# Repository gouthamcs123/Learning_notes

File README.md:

# Learning_notes
Documentation of what i studied during my training period

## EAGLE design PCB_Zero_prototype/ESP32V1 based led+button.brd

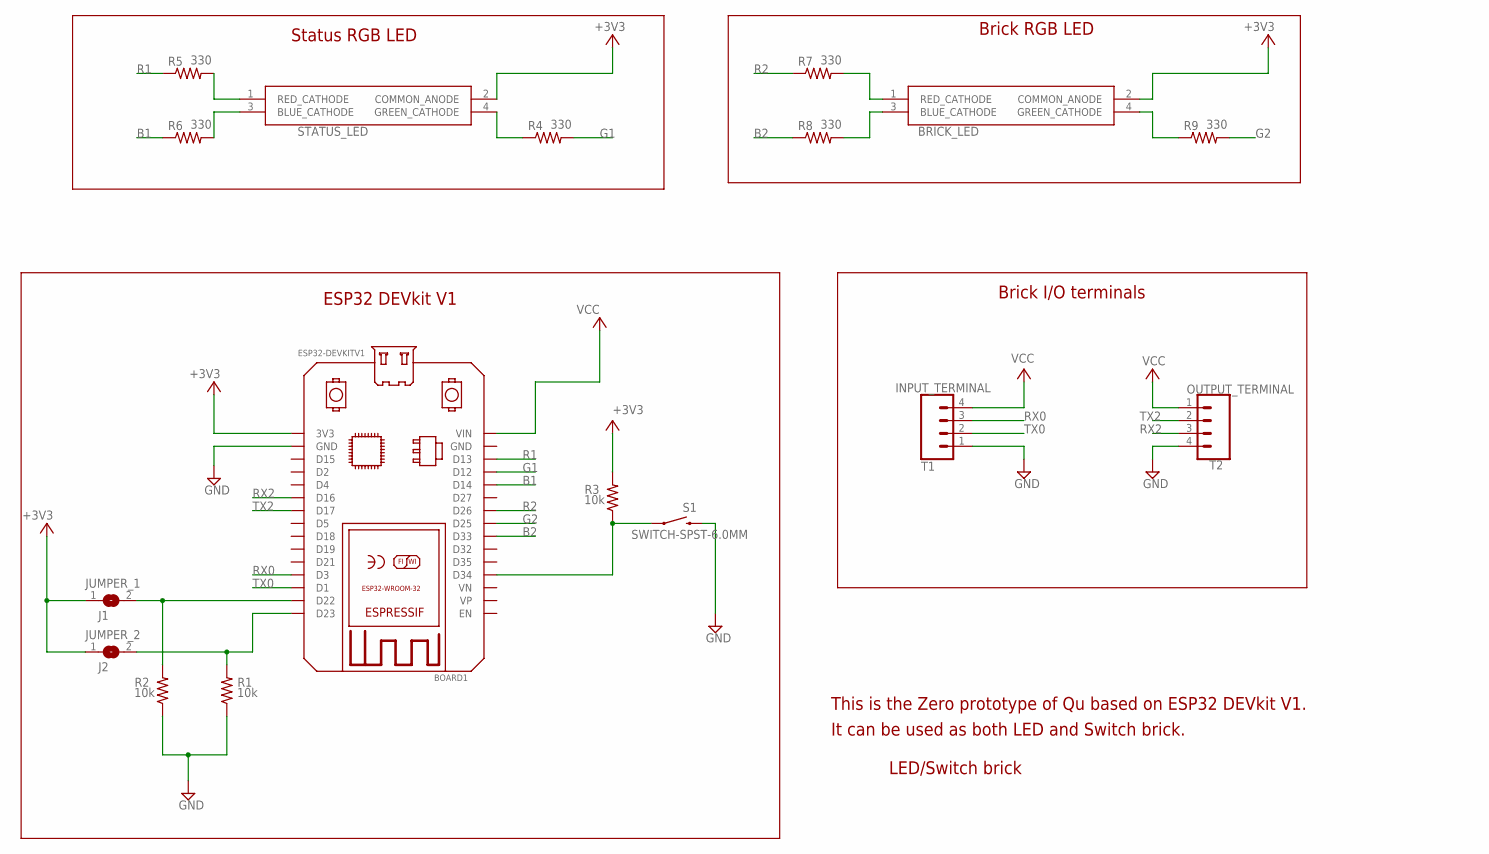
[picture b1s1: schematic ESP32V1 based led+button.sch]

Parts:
BOARD1: ESP32DEVKITV1; ESP32-DEVKITV1
BRICK_LED: WP154A4SEJ3VBDZGW_CA; L-154A4SUREQBFZGEC
INPUT_TERMINAL: T1; 1X04
JUMPER_1: J1; SJW
JUMPER_2: J2; SJW
OUTPUT_TERMINAL: T2; 1X04
R1, R2, R3: 10k; AXIAL-0.3
R4, R5, R6, R7, R8, R9: 330; AXIAL-0.3
S1: SWITCH-SPST-6.0MM; TACTILE_SWITCH_PTH_6.0MM_KIT
STATUS_LED: WP154A4SEJ3VBDZGW_CA; L-154A4SUREQBFZGEC

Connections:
+3V3: BOARD1.3V3, BRICK_LED.2 (COMMON_ANODE), JUMPER_1.1, JUMPER_2.1, R3.P$2 (2), STATUS_LED.2 (COMMON_ANODE)
B1: BOARD1.D14, R6.P$1 (1)
B2: BOARD1.D33, R8.P$1 (1)
G1: BOARD1.D12, R4.P$2 (2)
G2: BOARD1.D25, R9.P$2 (2)
GND: BOARD1.GND@1 (GND), INPUT_TERMINAL.1, OUTPUT_TERMINAL.4, R1.P$1 (1), R2.P$1 (1), S1.3 (2)
unnamed: BOARD1.D22, JUMPER_1.2, R2.P$2 (2)
unnamed: BOARD1.D23, JUMPER_2.2, R1.P$2 (2)
unnamed: R6.P$2 (2), STATUS_LED.3 (BLUE_CATHODE)
unnamed: R5.P$2 (2), STATUS_LED.1 (RED_CATHODE)
unnamed: BOARD1.D34, R3.P$1 (1), S1.1
unnamed: R4.P$1 (1), STATUS_LED.4 (GREEN_CATHODE)
unnamed: BRICK_LED.3 (BLUE_CATHODE), R8.P$2 (2)
unnamed: BRICK_LED.1 (RED_CATHODE), R7.P$2 (2)
unnamed: BRICK_LED.4 (GREEN_CATHODE), R9.P$1 (1)
R1: BOARD1.D13, R5.P$1 (1)
R2: BOARD1.D26, R7.P$1 (1)
RX0: BOARD1.D3, INPUT_TERMINAL.3
RX2: BOARD1.D16, OUTPUT_TERMINAL.3
TX0: BOARD1.D1, INPUT_TERMINAL.2
TX2: BOARD1.D17, OUTPUT_TERMINAL.2
VCC: BOARD1.VIN, INPUT_TERMINAL.4, OUTPUT_TERMINAL.1

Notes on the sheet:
LED/Switch brick
This is the Zero prototype of Qu based on ESP32 DEVkit V1.
It can be used as both LED and Switch brick.
Brick I/O terminals
Status RGB LED
Brick RGB LED
ESP32 DEVkit V1

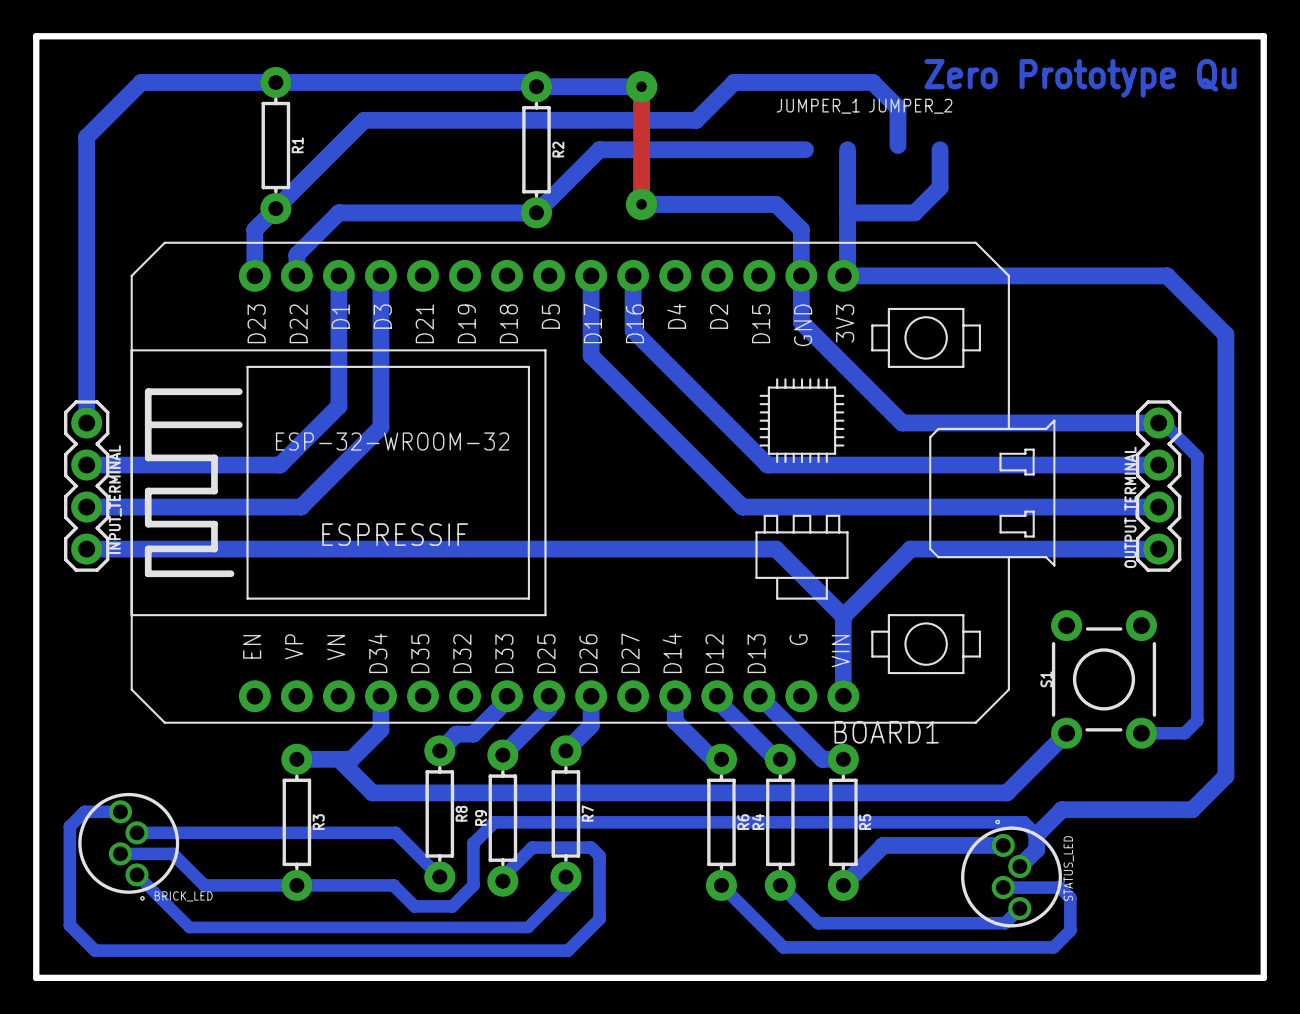
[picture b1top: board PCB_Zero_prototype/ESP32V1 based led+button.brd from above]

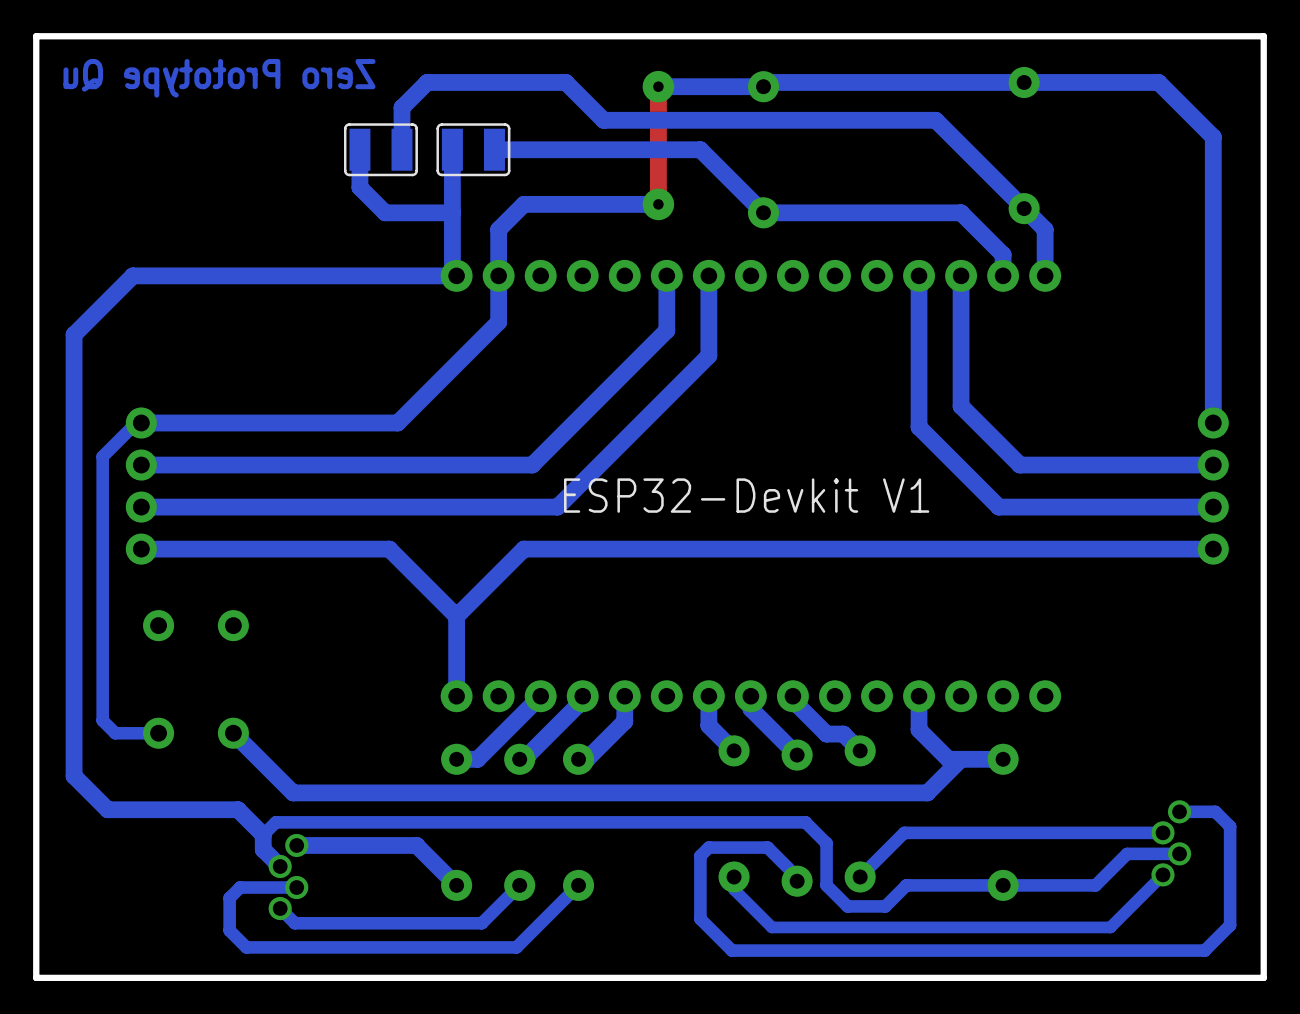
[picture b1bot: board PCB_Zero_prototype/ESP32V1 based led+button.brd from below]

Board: 2 copper layers, 74.2 x 56.9 mm, 17 parts (2 on the bottom side), 22 nets.

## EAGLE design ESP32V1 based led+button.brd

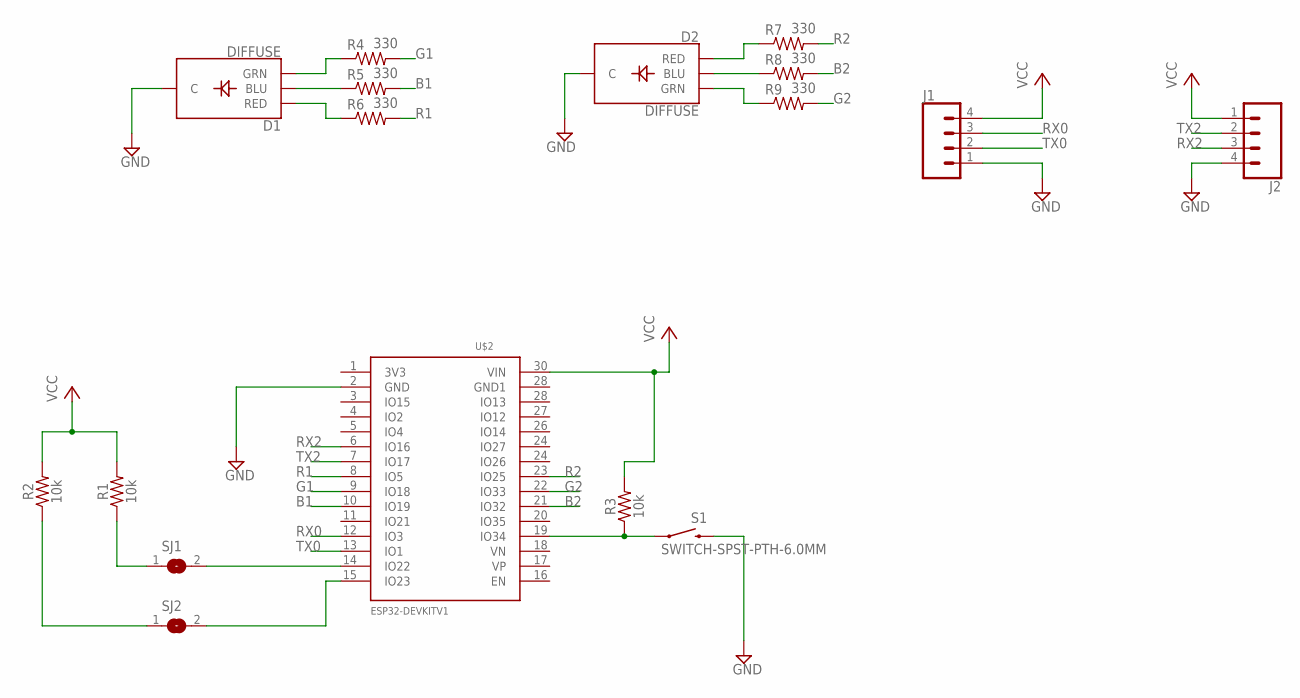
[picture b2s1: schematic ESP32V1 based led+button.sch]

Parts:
D1, D2: DIFFUSE; LED-RGB-THRU
J1, J2: CONN_04; 1X04
R1, R2, R3: 10k; AXIAL-0.3
R4, R5, R6, R7, R8, R9: 330; AXIAL-0.3
S1: SWITCH-SPST-PTH-6.0MM; TACTILE_SWITCH_PTH_6.0MM_KIT
SJ1, SJ2: SJW
U$2: ESP32DEVKITV1; ESP32-DEVKITV1

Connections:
B1: R5.P$2 (2), U$2.10 (IO19)
B2: R8.P$2 (2), U$2.21 (IO32)
G1: R4.P$2 (2), U$2.9 (IO18)
G2: R9.P$2 (2), U$2.22 (IO33)
GND: D1.2 (C), D2.2 (C), J1.1, J2.4, S1.3 (2), U$2.2 (GND)
unnamed: SJ2.2, U$2.15 (IO23)
unnamed: R2.P$1 (1), SJ2.1
unnamed: SJ1.2, U$2.14 (IO22)
unnamed: R1.P$1 (1), SJ1.1
unnamed: D1.3 (GRN), R4.P$1 (1)
unnamed: D1.4 (BLU), R5.P$1 (1)
unnamed: D1.1 (RED), R6.P$1 (1)
unnamed: D2.4 (BLU), R8.P$1 (1)
unnamed: R3.P$1 (1), S1.1, U$2.19 (IO34)
unnamed: D2.1 (RED), R7.P$1 (1)
unnamed: D2.3 (GRN), R9.P$1 (1)
R1: R6.P$2 (2), U$2.8 (IO5)
R2: R7.P$2 (2), U$2.23 (IO25)
RX0: J1.3, U$2.12 (IO3)
RX2: J2.3, U$2.6 (IO16)
TX0: J1.2, U$2.13 (IO1)
TX2: J2.2, U$2.7 (IO17)
VCC: J1.4, J2.1, R1.P$2 (2), R2.P$2 (2), R3.P$2 (2), U$2.30 (VIN)

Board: 2 copper layers, 17 parts (0 on the bottom side), 23 nets, no tracks yet.

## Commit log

2020-11-21 new file added
2020-11-21 heading code ettiquote added
2020-11-21 added file
2020-11-21 added about code etiquette
2020-11-21 version control heading
2020-11-21 software used
2020-11-21 eagle
2020-11-21 arduino
2020-11-22 added points
2020-11-22 added intro about edge connectors
2020-11-22 added content
2020-11-22 images added
2020-11-23 added
2020-11-23 added more connectors
2020-11-23 new file about work
2020-11-25 added image
2020-11-25 added files
2020-11-26 added data and files
2020-11-26 spring fingers deleted
2020-11-26 file again added
2020-11-26 added connector datasheet from TE connectivity
2020-11-27 added...
2020-11-30 documented
2020-11-30 edited and documented
2020-12-01 edited
2020-12-02 renamed file
2020-12-02 Delete anr.docx
    renamed it
2020-12-03 added file content structure
2020-12-04 added something
2020-12-08 protocol guide lines
2020-12-11 added pcb files
2020-12-13 edited files
2020-12-14 added edited schematic

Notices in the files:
parts and their libraries:
SparkFun-LED: Licensing: Creative Commons ShareAlike 4.0 International - https://creativecommons.org/licenses/by-sa/4.0
